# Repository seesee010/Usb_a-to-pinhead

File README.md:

# USB-A to Pinhead
This is just a really simple Converter

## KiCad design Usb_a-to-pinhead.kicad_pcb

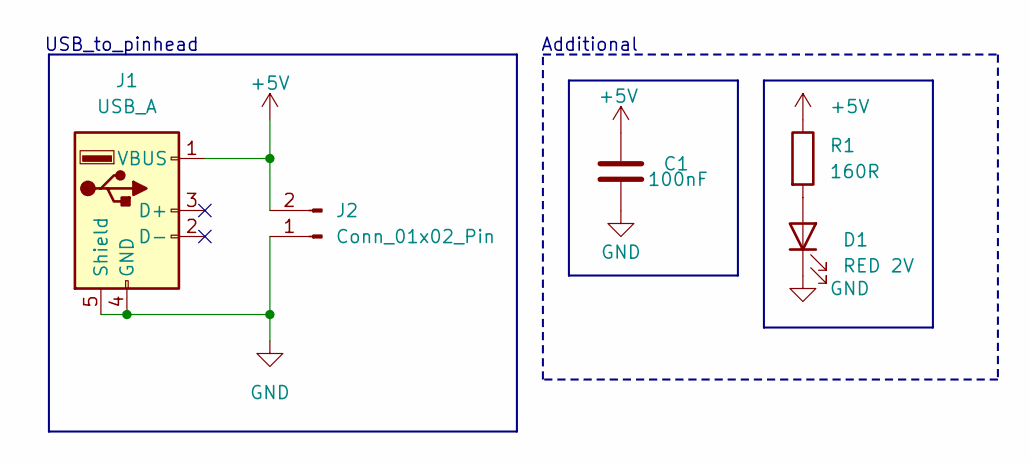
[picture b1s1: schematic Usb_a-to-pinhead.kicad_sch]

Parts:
C1: 100nF; C_0402_1005Metric
D1: RED 2V; LED_0201_0603Metric
J1: USB_A; USB_A_Molex_67643_Horizontal
J2: Conn_01x02_Pin; PinHeader_1x02_P2.54mm_Vertical
R1: 160R; R_0201_0603Metric

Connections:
+5V: C1.1, J1.1 (VBUS), J2.2, R1.1
GND: C1.2, D1.1 (K), J1.4 (GND), J1.5 (Shield), J2.1
unnamed: D1.2 (A), R1.2

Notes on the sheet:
Additional
USB_to_pinhead

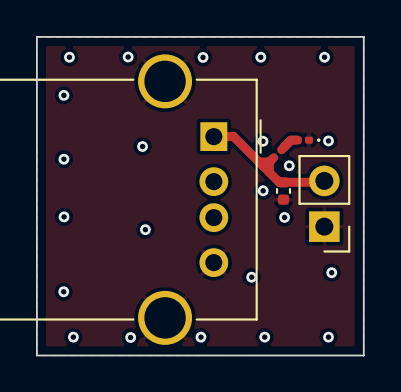
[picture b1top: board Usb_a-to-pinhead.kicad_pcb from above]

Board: 2 copper layers, 18.2 x 17.7 mm, 5 parts (0 on the bottom side), 3 nets.

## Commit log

2026-01-26 Initial
2026-01-26 Add project title and description to README
2026-03-09 2026-03-9 | So-Mo
